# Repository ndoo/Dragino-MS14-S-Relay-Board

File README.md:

# Dragino-MS14-S-Relay-Board

Darlington array 5V relay driver for the Dragino MS14-S. Plugs into the daughterboard header inside, provides high current 5V for driving motors, relays.

12V can’t be done because the MS14 sensor output pins have 6V ESD protection on them (excess voltage shunted to GND).

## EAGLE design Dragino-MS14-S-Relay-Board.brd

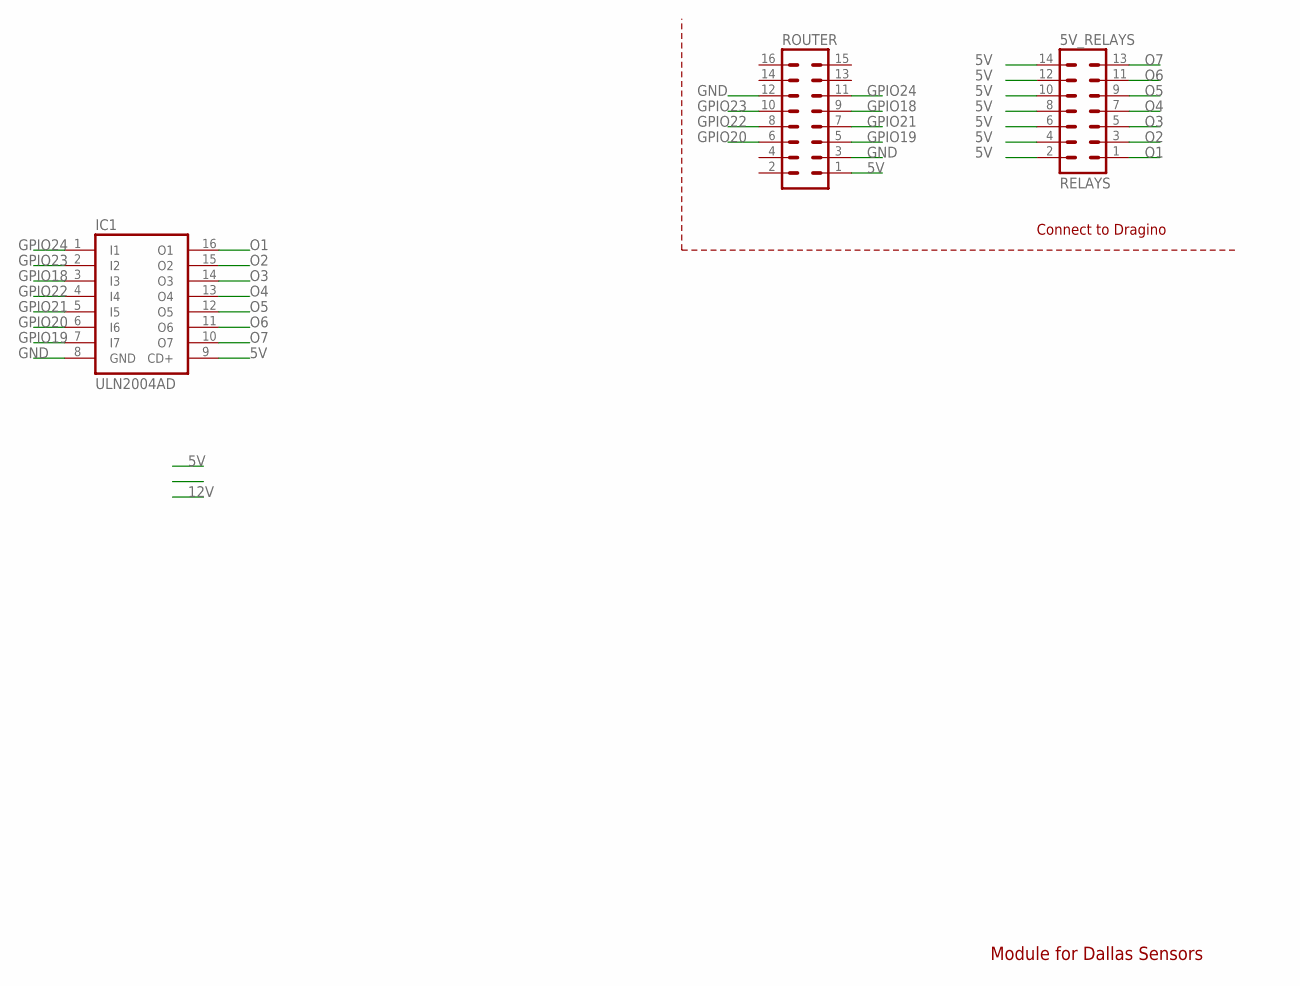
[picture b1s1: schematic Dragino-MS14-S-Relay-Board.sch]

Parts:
5V_RELAYS: RELAYS; MA07-2
IC1: ULN2004AD; SO16
ROUTER: MA08-2

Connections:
5V: 5V_RELAYS.2, 5V_RELAYS.4, 5V_RELAYS.6, 5V_RELAYS.8, 5V_RELAYS.10, 5V_RELAYS.12, 5V_RELAYS.14, IC1.9 (CD+), ROUTER.1
GND: IC1.8 (GND), ROUTER.3, ROUTER.12
GPIO18: IC1.3 (I3), ROUTER.9
GPIO19: IC1.7 (I7), ROUTER.5
GPIO20: IC1.6 (I6), ROUTER.6
GPIO21: IC1.5 (I5), ROUTER.7
GPIO22: IC1.4 (I4), ROUTER.8
GPIO23: IC1.2 (I2), ROUTER.10
GPIO24: IC1.1 (I1), ROUTER.11
O1: 5V_RELAYS.1, IC1.16 (O1)
O2: 5V_RELAYS.3, IC1.15 (O2)
O3: 5V_RELAYS.5, IC1.14 (O3)
O4: 5V_RELAYS.7, IC1.13 (O4)
O5: 5V_RELAYS.9, IC1.12 (O5)
O6: 5V_RELAYS.11, IC1.11 (O6)
O7: 5V_RELAYS.13, IC1.10 (O7)

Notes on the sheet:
Connect to Dragino
Module for Dallas Sensors

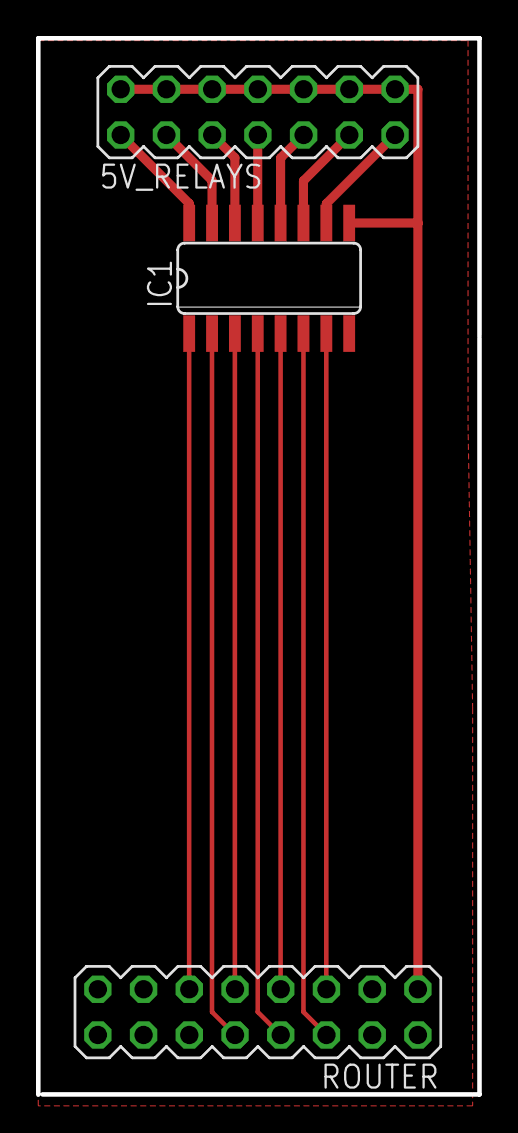
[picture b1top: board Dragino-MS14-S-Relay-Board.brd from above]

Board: 2 copper layers, 24.5 x 58.7 mm, 3 parts (0 on the bottom side), 16 nets.

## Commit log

2016-08-31 Initial work
2016-08-31 Create LICENSE

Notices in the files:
parts and their libraries:
frames: http://creativecommons.org/licenses/by-sa/3.0
frames: Released under the CC Attribution Share-Alike 3.0 License
